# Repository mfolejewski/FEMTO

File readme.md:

# Femto - RP2040 12x12mm PCB module

## Description

Femto is a ultra compact Raspberry Pi RP2040 module, which has features, as following:
- small footprint 12x12mm,
- all 30 GPIO pins connected,
- stamp form factor,
- 4-layer PCB board,
- onboard: QSPI Flash (USON8 package), 12MHz oscillator, PWR LED,
- fully open source project (OSHW).

Here you can find:
- \Photos: a few pictures of the assembled PCB boards
- \Python: simple script do test Femto module using Femto Tester board (use Thonny IDE)
- \manufacturing_files: all the production files for ordering PCB and assembly at JLCPCB (Gerber files, Pick & Place, BOM, etc.)
- \source_files: source files in Kicad and Altium Designer format

The main goal and reason to create this project was attempt to design as smallest as possible, and fully functional RP2040 module. Please note, that RP2040 MCU nas 7x7mm package, and Femto module has only a bit more, 12x12mm. In comparision, closer competitiors, such as Raspberry Pi Pico or RP2040 Stamp (Solder Party) have appropriately 51x21mm and 25x25mm.

The project consists of 3 parts:
- Module (mainboard)
- frame (solder frame)
- tester (testbench, only for functional verification)

## License

Project published as Open Source Hardware (OSHW) under CERN OHL v1.2 (Open Hardware Licence).

Project has been certified as Open Source Hardware by the Open Source Hardware Association (OSHWA).

UID is: PL000009

https://certification.oshwa.org/pl000009.html

## Press release:

[hackster.io](http://hackster.io/news/mirek-folejewski-s-femto-module-is-a-full-feature-raspberry-pi-rp2040-in-the-smallest-footprint-yet-d75727c4adbf.amp)

[cnx-software.com](https://cnx-software.com/2022/08/22/femto-tiny-raspberry-pi-rp2040-module/)

[blingeach.com](https://blingeach.com/mirek-folejewskis-femto-module-is-a-full-function-raspberry-pi-rp2040-within-the-smallest-footprint-but/)

[tecnohub.org](https://tecnohub.org/2022/08/a-full-featured-raspberry-pi-rp2040-in.html?m=1)

[theperfectech.com](https://theperfectech.com/mirek-folejewskis-femto-module-is-a-full-characteristic-raspberry-pi-rp2040-within-the-smallest-footprint-but/)

[hackaday.io](https://hackaday.io/project/186871-femto-module-v1)

## Photos

Raspberry Pico and Femto Module v1:

Femto Module:

Femto Frame:

Femto Tester:

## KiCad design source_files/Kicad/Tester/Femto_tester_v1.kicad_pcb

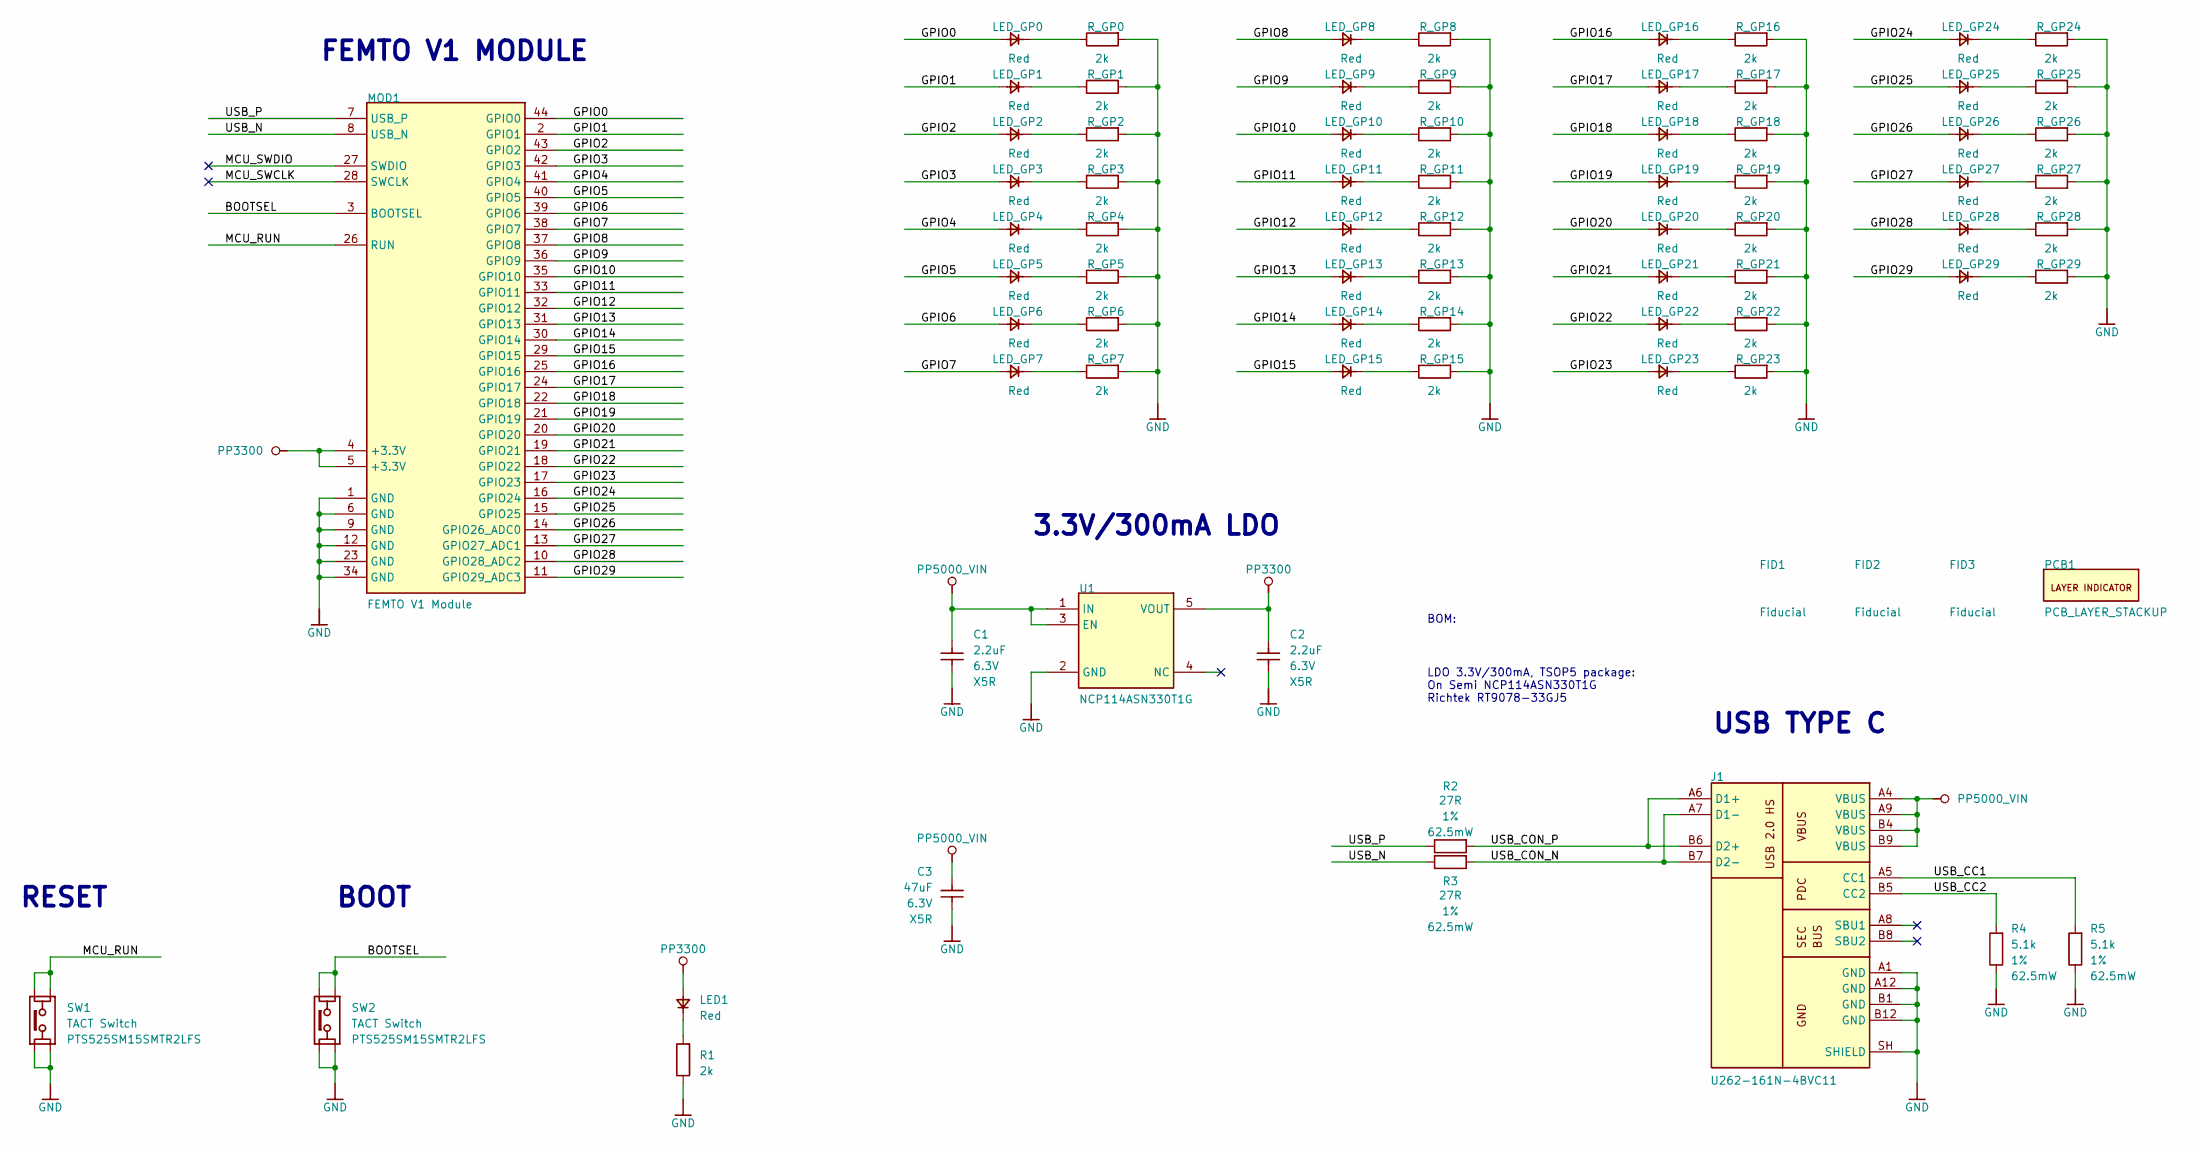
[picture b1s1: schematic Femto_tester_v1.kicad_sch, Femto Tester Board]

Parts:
C1, C2: 2.2uF; CAP_0402_R; VOLTAGE RATING 6.3V; TOLERANCE TBD; MPN CL05A225MQ5NNNC
C3: 47uF; CAP_0603_R; VOLTAGE RATING 6.3V; TOLERANCE TBD; MPN GENERIC
FID1, FID2, FID3: Fiducial; PCB_FID_RND_100x300
J1: U262-161N-4BVC11; CON_XKB_U262-161N-4BVC11; MPN U262-161N-4BVC11
LED1: Red; LED_0402_R
LED_GP0, LED_GP1, LED_GP2, LED_GP3, LED_GP4, LED_GP5, LED_GP6, LED_GP7, LED_GP8, LED_GP9, LED_GP10, LED_GP11, LED_GP12, LED_GP13, LED_GP14, LED_GP15, LED_GP16, LED_GP17, LED_GP18, LED_GP19, LED_GP20, LED_GP21, LED_GP22, LED_GP23, LED_GP24, LED_GP25, LED_GP26, LED_GP27, LED_GP28, LED_GP29: Red; LED_0402_R
MOD1: FEMTO V1 Module; _Biblioteki_MirFol_nowe_Pineberry_Lib.PcbLib_MOD_FEMTO_V1_1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
PCB1: PCB_LAYER_STACKUP; PCB_STACKUP-2L_A1
R1: 2k; RES_0402_R; TOLERANCE 1%; POWER RATING 62.5mW; MPN RC0402FR-072KP
R2, R3: 27R; RES_0402_R; TOLERANCE 1%; POWER RATING 62.5mW; MPN RC0402FR-0727RL
R4, R5: 5.1k; RES_0402_R; TOLERANCE 1%; POWER RATING 62.5mW; MPN RC0402FR-075K1L
R_GP0, R_GP1, R_GP2, R_GP3, R_GP4, R_GP5, R_GP6, R_GP7, R_GP8, R_GP9, R_GP10, R_GP11, R_GP12, R_GP13, R_GP14, R_GP15, R_GP16, R_GP17, R_GP18, R_GP19, R_GP20, R_GP21, R_GP22, R_GP23, R_GP24, R_GP25, R_GP26, R_GP27, R_GP28, R_GP29: 2k; RES_0402_R; TOLERANCE 1%; POWER RATING 62.5mW; MPN RC0402FR-072KP
SW1, SW2: TACT Switch; SWI_CKS_PTS525; MPN PTS525SM15SMTR2LFS
U1: NCP114ASN330T1G; _Biblioteki_MirFol_nowe_SH_lib.PcbLib_ICC_TSOT-5_290X160H11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; MPN NCP114ASN330T1G

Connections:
/BOOTSEL: MOD1.3 (BOOTSEL), SW2.1, SW2.2
/GPIO0: LED_GP0.2, MOD1.44 (GPIO0)
/GPIO1: LED_GP1.2, MOD1.2 (GPIO1)
/GPIO2: LED_GP2.2, MOD1.43 (GPIO2)
/GPIO3: LED_GP3.2, MOD1.42 (GPIO3)
/GPIO4: LED_GP4.2, MOD1.41 (GPIO4)
/GPIO5: LED_GP5.2, MOD1.40 (GPIO5)
/GPIO6: LED_GP6.2, MOD1.39 (GPIO6)
/GPIO7: LED_GP7.2, MOD1.38 (GPIO7)
/GPIO8: LED_GP8.2, MOD1.37 (GPIO8)
/GPIO9: LED_GP9.2, MOD1.36 (GPIO9)
/GPIO10: LED_GP10.2, MOD1.35 (GPIO10)
/GPIO11: LED_GP11.2, MOD1.33 (GPIO11)
/GPIO12: LED_GP12.2, MOD1.32 (GPIO12)
/GPIO13: LED_GP13.2, MOD1.31 (GPIO13)
/GPIO14: LED_GP14.2, MOD1.30 (GPIO14)
/GPIO15: LED_GP15.2, MOD1.29 (GPIO15)
/GPIO16: LED_GP16.2, MOD1.25 (GPIO16)
/GPIO17: LED_GP17.2, MOD1.24 (GPIO17)
/GPIO18: LED_GP18.2, MOD1.22 (GPIO18)
/GPIO19: LED_GP19.2, MOD1.21 (GPIO19)
/GPIO20: LED_GP20.2, MOD1.20 (GPIO20)
/GPIO21: LED_GP21.2, MOD1.19 (GPIO21)
/GPIO22: LED_GP22.2, MOD1.18 (GPIO22)
/GPIO23: LED_GP23.2, MOD1.17 (GPIO23)
/GPIO24: LED_GP24.2, MOD1.16 (GPIO24)
/GPIO25: LED_GP25.2, MOD1.15 (GPIO25)
/GPIO26: LED_GP26.2, MOD1.14 (GPIO26_ADC0)
/GPIO27: LED_GP27.2, MOD1.13 (GPIO27_ADC1)
/GPIO28: LED_GP28.2, MOD1.10 (GPIO28_ADC2)
/GPIO29: LED_GP29.2, MOD1.11 (GPIO29_ADC3)
/MCU_RUN: MOD1.26 (RUN), SW1.1, SW1.2
/MCU_SWCLK: MOD1.28 (SWCLK)
/MCU_SWDIO: MOD1.27 (SWDIO)
/USB_CC1: J1.A5 (CC1), R5.2
/USB_CC2: J1.B5 (CC2), R4.2
/USB_CON_N: J1.A7 (D1-), J1.B7 (D2-), R3.2
/USB_CON_P: J1.A6 (D1+), J1.B6 (D2+), R2.2
/USB_N: MOD1.8 (USB_N), R3.1
/USB_P: MOD1.7 (USB_P), R2.1
GND: C1.1, C2.1, C3.1, J1.A1 (GND), J1.A12 (GND), J1.B1 (GND), J1.B12 (GND), J1.SH (SHIELD), MOD1.1 (GND), MOD1.6 (GND), MOD1.9 (GND), MOD1.12 (GND), MOD1.23 (GND), MOD1.34 (GND), R1.1, R4.1, R5.1, R_GP0.1, R_GP1.1, R_GP2.1, R_GP3.1, R_GP4.1, R_GP5.1, R_GP6.1, R_GP7.1, R_GP8.1, R_GP9.1, R_GP10.1, R_GP11.1, R_GP12.1, R_GP13.1, R_GP14.1, R_GP15.1, R_GP16.1, R_GP17.1, R_GP18.1, R_GP19.1, R_GP20.1, R_GP21.1, R_GP22.1, R_GP23.1, R_GP24.1, R_GP25.1, R_GP26.1, R_GP27.1, R_GP28.1, R_GP29.1, SW1.3, SW1.4, SW2.3, SW2.4, U1.2 (GND)
unnamed: LED1.1, R1.2
unnamed: LED_GP0.1, R_GP0.2
unnamed: LED_GP1.1, R_GP1.2
unnamed: LED_GP2.1, R_GP2.2
unnamed: LED_GP3.1, R_GP3.2
unnamed: LED_GP4.1, R_GP4.2
unnamed: LED_GP5.1, R_GP5.2
unnamed: LED_GP6.1, R_GP6.2
unnamed: LED_GP7.1, R_GP7.2
unnamed: LED_GP8.1, R_GP8.2
unnamed: LED_GP9.1, R_GP9.2
unnamed: LED_GP10.1, R_GP10.2
unnamed: LED_GP11.1, R_GP11.2
unnamed: LED_GP12.1, R_GP12.2
unnamed: LED_GP13.1, R_GP13.2
unnamed: LED_GP14.1, R_GP14.2
unnamed: LED_GP15.1, R_GP15.2
unnamed: LED_GP16.1, R_GP16.2
unnamed: LED_GP17.1, R_GP17.2
unnamed: LED_GP18.1, R_GP18.2
unnamed: LED_GP19.1, R_GP19.2
unnamed: LED_GP20.1, R_GP20.2
unnamed: LED_GP21.1, R_GP21.2
unnamed: LED_GP22.1, R_GP22.2
unnamed: LED_GP23.1, R_GP23.2
unnamed: LED_GP24.1, R_GP24.2
unnamed: LED_GP25.1, R_GP25.2
unnamed: LED_GP26.1, R_GP26.2
unnamed: LED_GP27.1, R_GP27.2
unnamed: LED_GP28.1, R_GP28.2
unnamed: LED_GP29.1, R_GP29.2
PP3300: C2.2, LED1.2, MOD1.4 (+3.3V), MOD1.5 (+3.3V), U1.5 (VOUT)
PP5000_VIN: C1.2, C3.2, J1.A4 (VBUS), J1.A9 (VBUS), J1.B4 (VBUS), J1.B9 (VBUS), U1.1 (IN), U1.3 (EN)

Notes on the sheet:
BOM:
USB TYPE C
BOOT
3.3V/300mA LDO
FEMTO V1 MODULE
RESET
LDO 3.3V/300mA, TSOP5 package: On Semi NCP114ASN330T1G Richtek RT9078-33GJ5

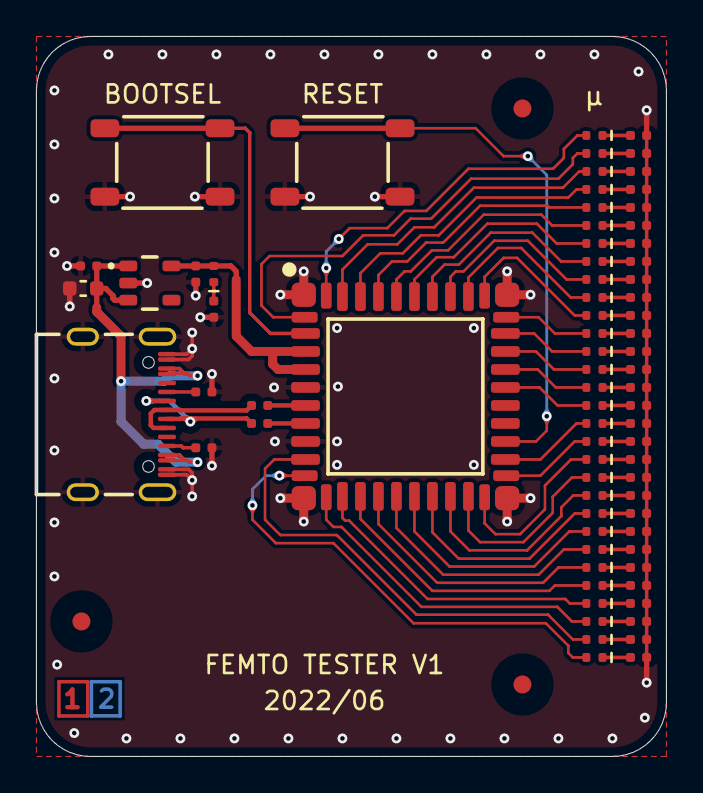
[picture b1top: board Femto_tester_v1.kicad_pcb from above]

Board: 2 copper layers, 35.0 x 40.0 mm, 78 parts (0 on the bottom side), 72 nets.

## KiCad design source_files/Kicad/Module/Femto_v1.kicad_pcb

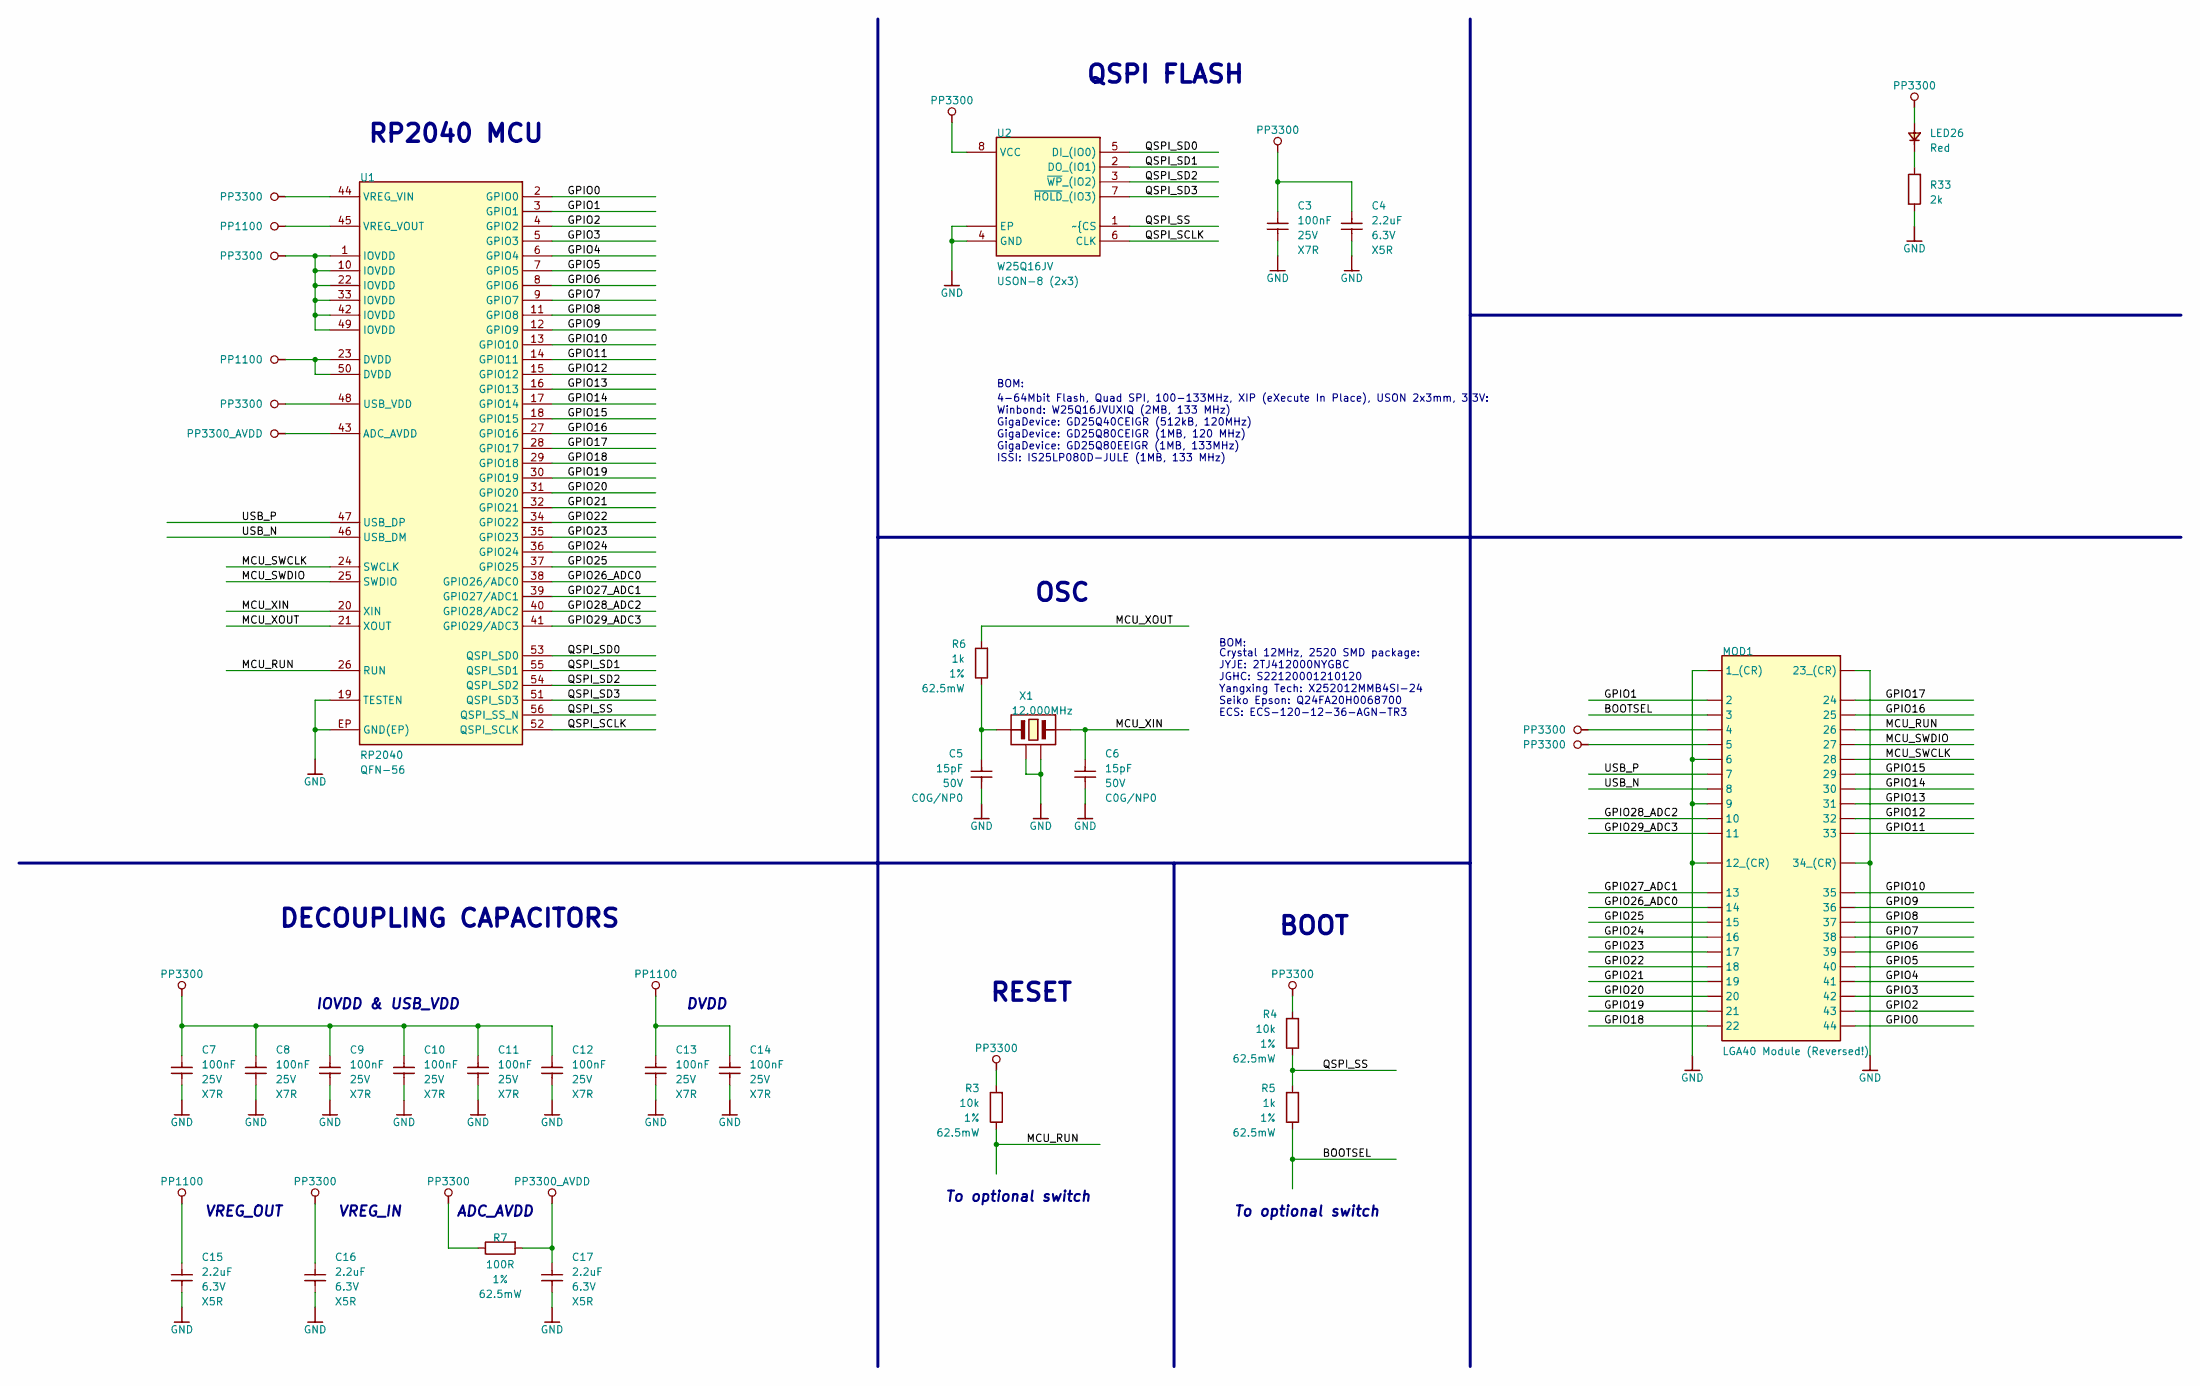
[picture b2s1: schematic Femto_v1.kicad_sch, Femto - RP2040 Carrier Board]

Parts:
C3, C7, C8, C9, C10, C11, C12, C13, C14: 100nF; CAP_0402_R; VOLTAGE RATING 25V; TOLERANCE TBD; MPN CL05B104KA5NNNC
C4, C15, C16, C17: 2.2uF; CAP_0402_R; VOLTAGE RATING 6.3V; TOLERANCE TBD; MPN CL05A225MQ5NNNC
C5, C6: 15pF; CAP_0402_R; VOLTAGE RATING 50V; TOLERANCE TBD; MPN C0402C150J5GACTU
LED26: Red; LED_0402_R
MOD1: LGA40 Module (Reversed!); PCB_LGA40_120X120_P100_REV
R3, R4: 10k; RES_0402_R; TOLERANCE 1%; POWER RATING 62.5mW; MPN RC0402FR-0710KL
R5, R6: 1k; RES_0402_R; TOLERANCE 1%; POWER RATING 62.5mW; MPN RC0402FR-071KL
R7: 100R; RES_0402_R; TOLERANCE 1%; POWER RATING 62.5mW; MPN RC0402FR-07100RL
R33: 2k; RES_0402_R; TOLERANCE 1%; POWER RATING 62.5mW; MPN RC0402FR-072KP
U1: RP2040; ICC_QFN56_700X700X90_P40_EP_RP2040; MPN RP2040
U2: W25Q16JV; ICC_USON8_200X300X55P50_EP; MPN W25Q16JVUXIQ
X1: 12.000MHz; OSC_2520_4P_250X200H50_R; MPN ECS-120-12-36-AGN-TR3

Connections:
/BOOTSEL: MOD1.3, R5.1
/GPIO0: MOD1.44, U1.2 (GPIO0)
/GPIO1: MOD1.2, U1.3 (GPIO1)
/GPIO2: MOD1.43, U1.4 (GPIO2)
/GPIO3: MOD1.42, U1.5 (GPIO3)
/GPIO4: MOD1.41, U1.6 (GPIO4)
/GPIO5: MOD1.40, U1.7 (GPIO5)
/GPIO6: MOD1.39, U1.8 (GPIO6)
/GPIO7: MOD1.38, U1.9 (GPIO7)
/GPIO8: MOD1.37, U1.11 (GPIO8)
/GPIO9: MOD1.36, U1.12 (GPIO9)
/GPIO10: MOD1.35, U1.13 (GPIO10)
/GPIO11: MOD1.33, U1.14 (GPIO11)
/GPIO12: MOD1.32, U1.15 (GPIO12)
/GPIO13: MOD1.31, U1.16 (GPIO13)
/GPIO14: MOD1.30, U1.17 (GPIO14)
/GPIO15: MOD1.29, U1.18 (GPIO15)
/GPIO16: MOD1.25, U1.27 (GPIO16)
/GPIO17: MOD1.24, U1.28 (GPIO17)
/GPIO18: MOD1.22, U1.29 (GPIO18)
/GPIO19: MOD1.21, U1.30 (GPIO19)
/GPIO20: MOD1.20, U1.31 (GPIO20)
/GPIO21: MOD1.19, U1.32 (GPIO21)
/GPIO22: MOD1.18, U1.34 (GPIO22)
/GPIO23: MOD1.17, U1.35 (GPIO23)
/GPIO24: MOD1.16, U1.36 (GPIO24)
/GPIO25: MOD1.15, U1.37 (GPIO25)
/GPIO26_ADC0: MOD1.14, U1.38 (GPIO26/ADC0)
/GPIO27_ADC1: MOD1.13, U1.39 (GPIO27/ADC1)
/GPIO28_ADC2: MOD1.10, U1.40 (GPIO28/ADC2)
/GPIO29_ADC3: MOD1.11, U1.41 (GPIO29/ADC3)
/MCU_RUN: MOD1.26, R3.1, U1.26 (RUN)
/MCU_SWCLK: MOD1.28, U1.24 (SWCLK)
/MCU_SWDIO: MOD1.27, U1.25 (SWDIO)
/MCU_XIN: C6.2, U1.20 (XIN), X1.3
/MCU_XOUT: R6.1, U1.21 (XOUT)
/QSPI_SCLK: U1.52 (QSPI_SCLK), U2.6 (CLK)
/QSPI_SD0: U1.53 (QSPI_SD0), U2.5 (DI_(IO0))
/QSPI_SD1: U1.55 (QSPI_SD1), U2.2 (DO_(IO1))
/QSPI_SD2: U1.54 (QSPI_SD2), U2.3 (~WP_(IO2))
/QSPI_SD3: U1.51 (QSPI_SD3), U2.7 (~HOLD_(IO3))
/QSPI_SS: R4.1, R5.2, U1.56 (QSPI_SS_N), U2.1 (~{CS)
/USB_N: MOD1.8, U1.46 (USB_DM)
/USB_P: MOD1.7, U1.47 (USB_DP)
GND: C3.1, C4.1, C5.1, C6.1, C7.1, C8.1, C9.1, C10.1, C11.1, C12.1, C13.1, C14.1, C15.1, C16.1, C17.1, MOD1.1 (1_(CR)), MOD1.6, MOD1.9, MOD1.12 (12_(CR)), MOD1.23 (23_(CR)), MOD1.34 (34_(CR)), R33.1, U1.19 (TESTEN), U1.EP (GND(EP)), U2.4 (GND), U2.EP, X1.2, X1.4
unnamed: C5.2, R6.2, X1.1
unnamed: LED26.1, R33.2
PP1100: C13.2, C14.2, C15.2, U1.23 (DVDD), U1.45 (VREG_VOUT), U1.50 (DVDD)
PP3300: C3.2, C4.2, C7.2, C8.2, C9.2, C10.2, C11.2, C12.2, C16.2, LED26.2, MOD1.4, MOD1.5, R3.2, R4.2, R7.2, U1.1 (IOVDD), U1.10 (IOVDD), U1.22 (IOVDD), U1.33 (IOVDD), U1.42 (IOVDD), U1.44 (VREG_VIN), U1.48 (USB_VDD), U1.49 (IOVDD), U2.8 (VCC)
PP3300_AVDD: C17.2, R7.1, U1.43 (ADC_AVDD)

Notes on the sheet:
To optional switch
ADC_AVDD
OSC
VREG_IN
RP2040 MCU
VREG_OUT
DVDD
IOVDD & USB_VDD
BOOT
QSPI FLASH
BOM:
4-64Mbit Flash, Quad SPI, 100-133MHz, XIP (eXecute In Place), USON 2x3mm, 3.3V: Winbond: W25Q16JVUXIQ (2MB, 133 MHz) GigaDevice: GD25Q40CEIGR (512kB, 120MHz) GigaDevice: GD25Q80CEIGR (1MB, 120 MHz) GigaDevice: GD25Q80EEIGR (1MB, 133MHz) ISSI: IS25LP080D-JULE (1MB, 133 MHz)
Crystal 12MHz, 2520 SMD package: JYJE: 2TJ412000NYGBC JGHC: S22120001210120 Yangxing Tech: X252012MMB4SI-24 Seiko Epson: Q24FA20H0068700 ECS: ECS-120-12-36-AGN-TR3
DECOUPLING CAPACITORS
RESET

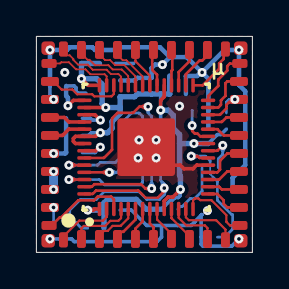
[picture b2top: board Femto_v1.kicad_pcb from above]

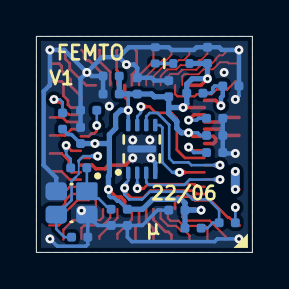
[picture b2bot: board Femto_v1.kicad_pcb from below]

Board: 4 copper layers, 12.0 x 12.0 mm, 26 parts (24 on the bottom side), 50 nets.

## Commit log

2022-08-26 Create LICENSE
